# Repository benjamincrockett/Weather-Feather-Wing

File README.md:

# Weather-Feather-Wing
 An online interactive viewer is available at https://kicanvas.org/. Copy and paste the URL of this repository into the text box on the KiCanvas website to get started. 

# Software
A software example for this project is available in the following repository: https://github.com/benjamincrockett/Air-Quality-Weather

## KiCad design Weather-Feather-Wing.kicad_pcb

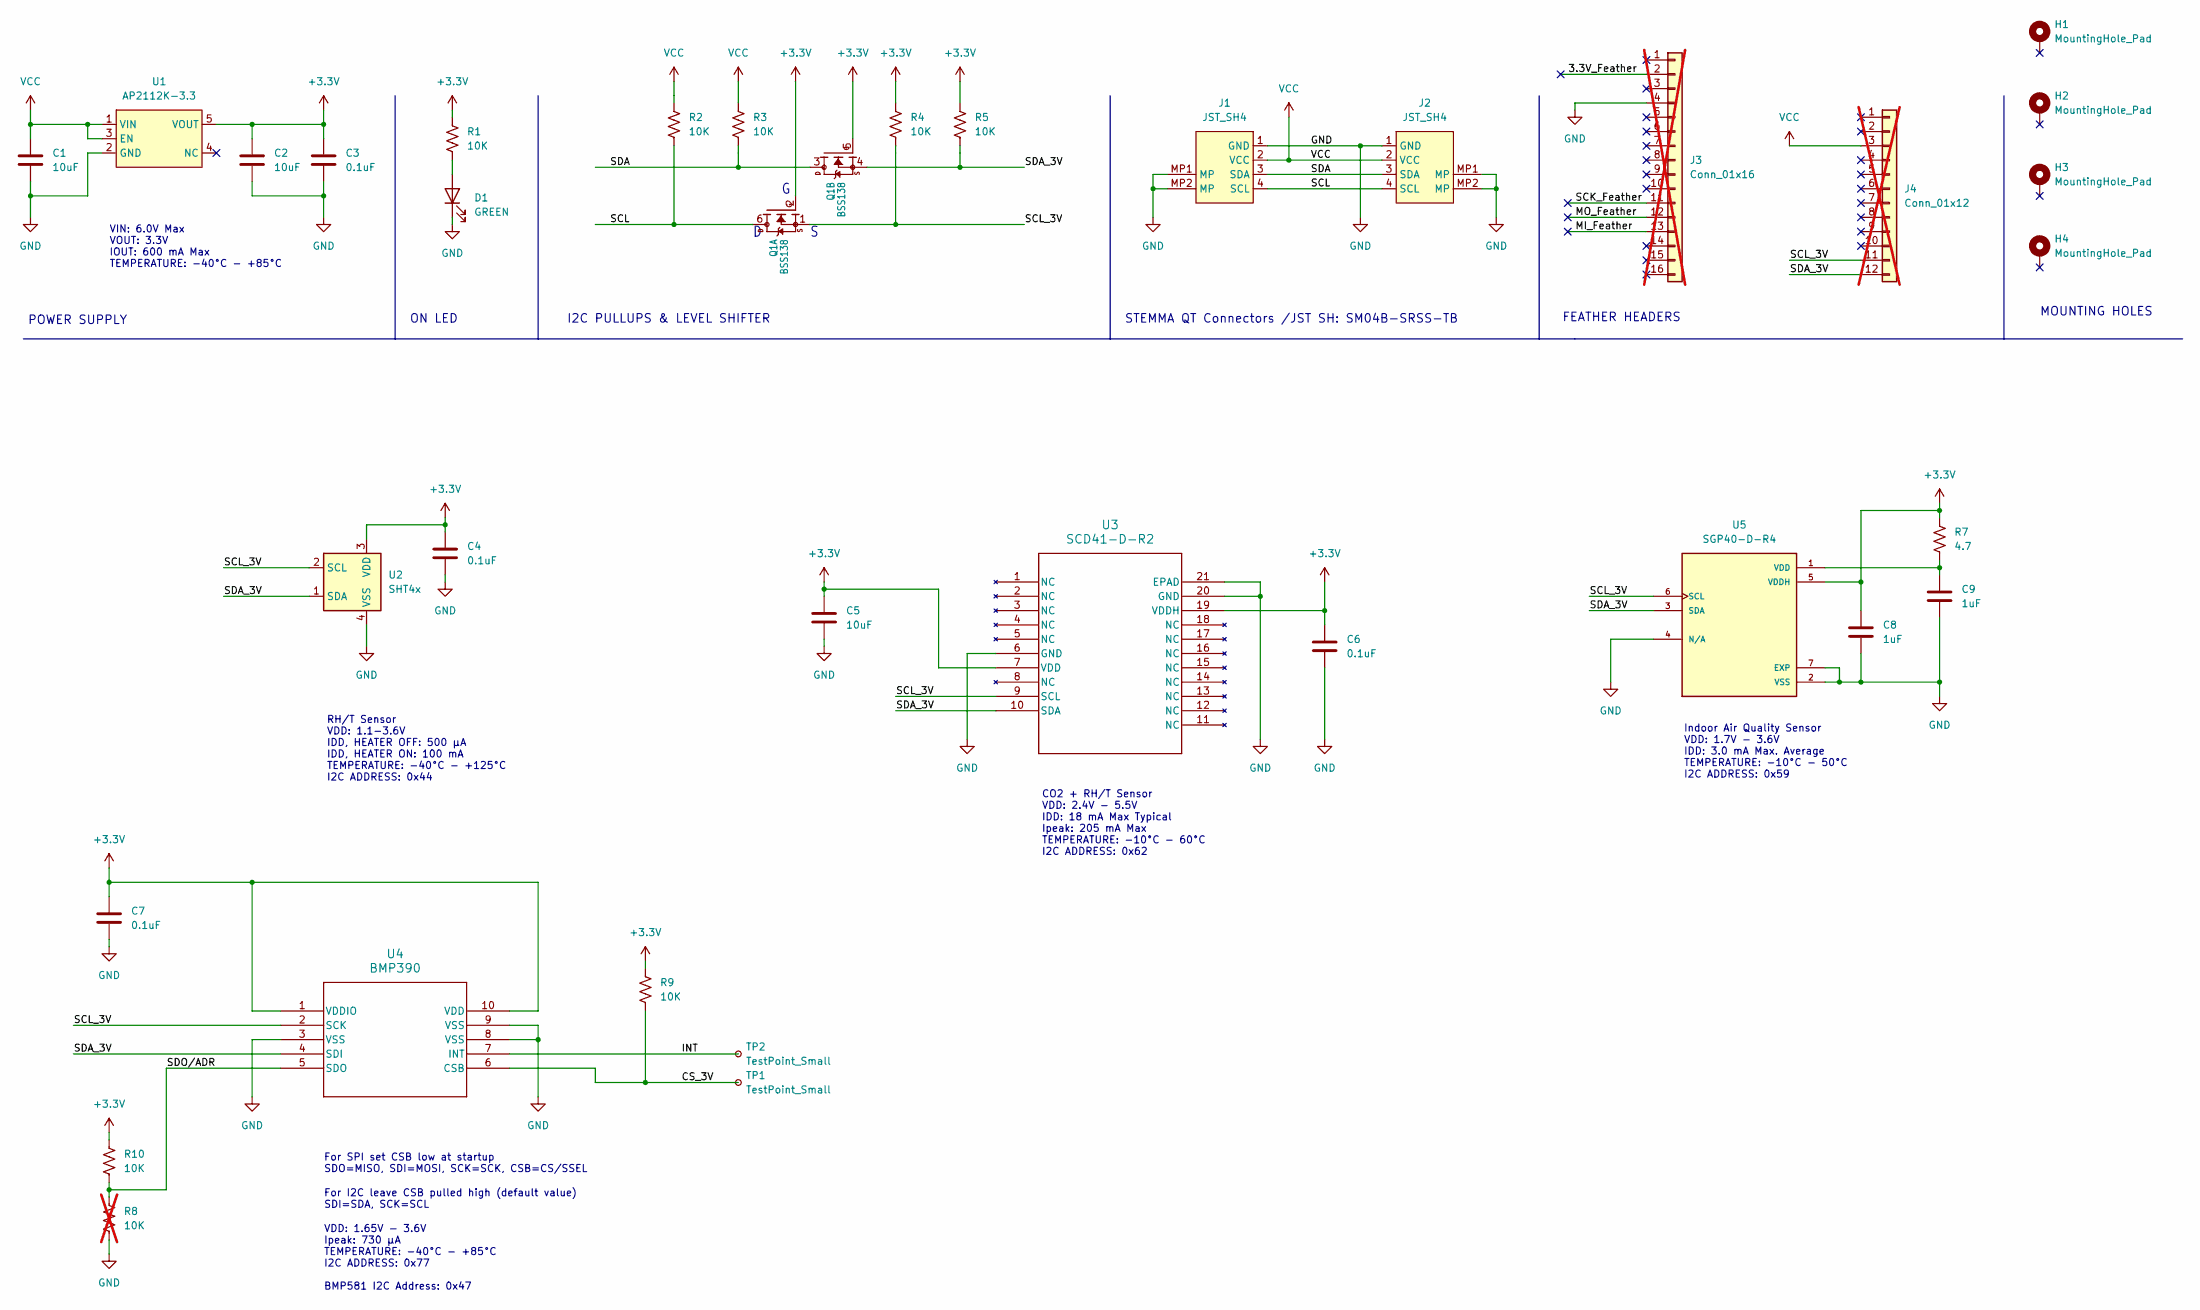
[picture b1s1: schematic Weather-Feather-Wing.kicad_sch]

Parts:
C1, C2, C5: 10uF; C_0805_2012Metric_Pad1.18x1.45mm_HandSolder
C3, C4, C6, C7: 0.1uF; C_0603_1608Metric_Pad1.08x0.95mm_HandSolder
C8, C9: 1uF; C_0603_1608Metric_Pad1.08x0.95mm_HandSolder
D1: GREEN; LED_0603_1608Metric_Pad1.05x0.95mm_HandSolder
H1, H2, H3, H4: MountingHole_Pad; MOUNTINGHOLE_2.5_PLATED
J1, J2: JST_SH4; JST_SH_SM04B-SRSS-TB_1x04-1MP_P1.00mm_Horizontal
J3: Conn_01x16; PinHeader_1x16_P2.54mm_Vertical; not fitted
J4: Conn_01x12; PinHeader_1x12_P2.54mm_Vertical; not fitted
Q1: BSS138; SOT363
R1, R2, R3, R4, R5, R9, R10: 10K; R_0603_1608Metric_Pad0.98x0.95mm_HandSolder
R7: 4.7; R_0603_1608Metric_Pad0.98x0.95mm_HandSolder
R8: 10K; R_0603_1608Metric_Pad0.98x0.95mm_HandSolder; not fitted
TP1, TP2: TestPoint_Small; TestPoint_Pad_D1.0mm
U1: AP2112K-3.3; SOT23-5
U2: SHT4x; SHT4X
U3: SCD41-D-R2; QFN20_SCD41-D-R2_SEN
U4: BMP390; 10LGA_2X2X0p75_BOS
U5: SGP40-D-R4; XCDR_SGP40-D-R4; PARTREV 1.2

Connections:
+3.3V: C2.1, C3.1, C4.1, C5.1, C6.1, C7.1, C8.1, Q1.2 (G), Q1.5 (G), R1.1, R4.1, R5.1, R7.1, R9.1, R10.1, U1.5 (VOUT), U2.3 (VDD), U3.7 (VDD), U3.19 (VDDH), U4.1 (VDDIO), U4.10 (VDD), U5.5 (VDDH)
/3.3V_Feather: J3.2
/CS_3V: R9.2, TP1.1, U4.6 (CSB)
/INT: TP2.1, U4.7 (INT)
/MI_Feather: J3.13
/MO_Feather: J3.12
/SCK_Feather: J3.11
/SCL: J1.4 (SCL), J2.4 (SCL), Q1.6 (D), R2.2
/SCL_3V: J4.11, Q1.1 (S), R4.2, U2.2 (SCL), U3.9 (SCL), U4.2 (SCK), U5.6 (SCL)
/SDA: J1.3 (SDA), J2.3 (SDA), Q1.3 (D), R3.2
/SDA_3V: J4.12, Q1.4 (S), R5.2, U2.1 (SDA), U3.10 (SDA), U4.4 (SDI), U5.3 (SDA)
/SDO/ADR: R8.2, R10.2, U4.5 (SDO)
GND: C1.2, C2.2, C3.2, C4.2, C5.2, C6.2, C7.2, C8.2, C9.2, D1.1 (K), J1.1 (GND), J1.MP1 (MP), J1.MP2 (MP), J2.1 (GND), J2.MP1 (MP), J2.MP2 (MP), J3.4, R8.1, U1.2 (GND), U2.4 (VSS), U3.6 (GND), U3.20 (GND), U3.21 (EPAD), U4.3 (VSS), U4.8 (VSS), U4.9 (VSS), U5.2 (VSS), U5.4 (N/A), U5.7 (EXP)
unnamed: D1.2 (A), R1.2
unnamed: C9.1, R7.2, U5.1 (VDD)
VCC: C1.1, J1.2 (VCC), J2.2 (VCC), J4.3, R2.1, R3.1, U1.1 (VIN), U1.3 (EN)

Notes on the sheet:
ON LED
POWER SUPPLY
I2C PULLUPS & LEVEL SHIFTER
RH/T Sensor VDD: 1.1-3.6V IDD, HEATER OFF: 500 µA IDD, HEATER ON: 100 mA TEMPERATURE: -40°C - +125°C I2C ADDRESS: 0x44
FEATHER HEADERS
MOUNTING HOLES
VIN: 6.0V Max VOUT: 3.3V IOUT: 600 mA Max TEMPERATURE: -40°C - +85°C
VDD: 1.65V - 3.6V Ipeak: 730 µA TEMPERATURE: -40°C - +85°C I2C ADDRESS: 0x77 BMP581 I2C Address: 0x47
STEMMA QT Connectors /JST SH: SM04B-SRSS-TB
Indoor Air Quality Sensor VDD: 1.7V - 3.6V IDD: 3.0 mA Max. Average TEMPERATURE: -10°C - 50°C I2C ADDRESS: 0x59
CO2 + RH/T Sensor VDD: 2.4V - 5.5V IDD: 18 mA Max Typical Ipeak: 205 mA Max TEMPERATURE: -10°C - 60°C I2C ADDRESS: 0x62
For I2C leave CSB pulled high (default value) SDI=SDA, SCK=SCL
For SPI set CSB low at startup SDO=MISO, SDI=MOSI, SCK=SCK, CSB=CS/SSEL

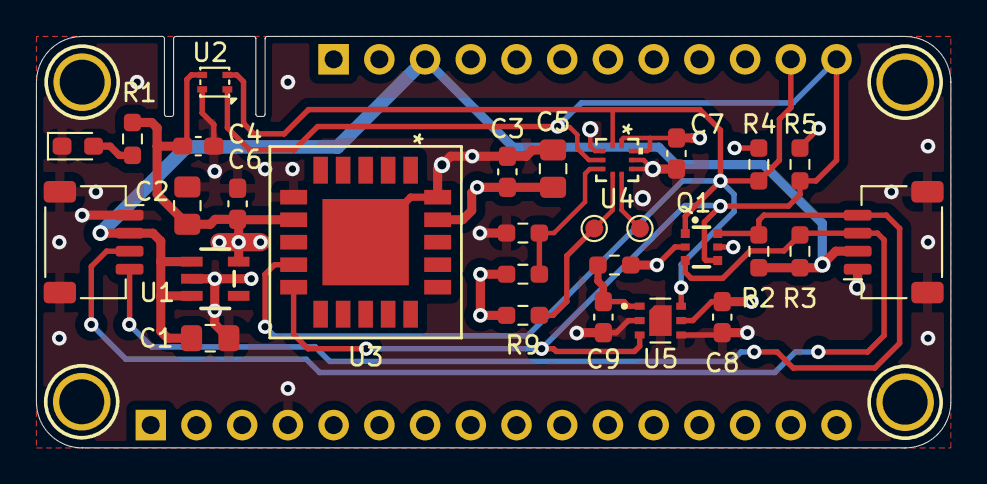
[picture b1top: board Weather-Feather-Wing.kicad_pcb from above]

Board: 4 copper layers, 50.8 x 22.9 mm, 35 parts (0 on the bottom side), 12 nets.

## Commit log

2025-03-22 Initial Release
2025-03-25 Corrections and improvements.
2025-03-26 As ordered from OSH Park.
2025-04-07 Cleanup and updates
2025-04-23 Updates after building the board.
2025-05-02 Design corrections, moved both header pins 50 mils closer to their respective edges.
2025-05-02 Adding test code to the repo.
2025-06-06 Added the PowerPoint file for the presentation.
